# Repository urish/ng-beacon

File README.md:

# ng-beacon

[Physical Web Beacon](https://medium.com/@urish/exploring-the-physical-web-without-buying-beacons-efae51e36c2e) shaped after the [Angular](https://angular.io) logo with JavaScript support

Copyright (C) 2016, 2017 Uri Shaked

## Build your own beacon

Check out the [BOM](BOM.md) file for the list of materials. In addition, you need to get the [PCB](hardware/) printed, I got mine from [PCBWay](http://www.pcbway.com).

## Features

- Physical Web (Eddystone) Beacon
- iBeacon
- Built-in [JavaScript Interpreter](https://www.espruino.com/Reference)
- Fully programmable via JavaScript
- Over-the-air firmware updates
- Prototyping area where you can add your own sensors and extend the board
- Runs of CR2032 / CR2024 coin cell battery, can last for several months
- Built in LED and push button

## Hardware
The board uses the [nRF52832 chip](https://www.nordicsemi.com/eng/Products/Bluetooth-low-energy/nRF52832), which has the following features:

- 32-bit ARM Cortex-M4F Processor running at 64MHz
- 512kB flash + 64kB RAM
- Bluetooth 5 support, up to 2MBPS
- Up to +4dBm output power, -96dBm sensitivity
- 3 PWM, 3 SPI, 2 I²C, Serial UART

## Code samples

Configure the built-in button to control the LED:

    setWatch(() => LED1.toggle(), BTN1, { 
      repeat: true,
      edge: 'falling', 
      debounce: 100
    });

[More code samples](examples/)

## Firmware

The current firmware is based on [Espruino](espruino.com). The latest source code [can be found here](https://github.com/urish/Espruino/tree/ng-beacon), and the most recent firmware build can be found in [this repo](https://github.com/urish/ng-beacon-firmware).

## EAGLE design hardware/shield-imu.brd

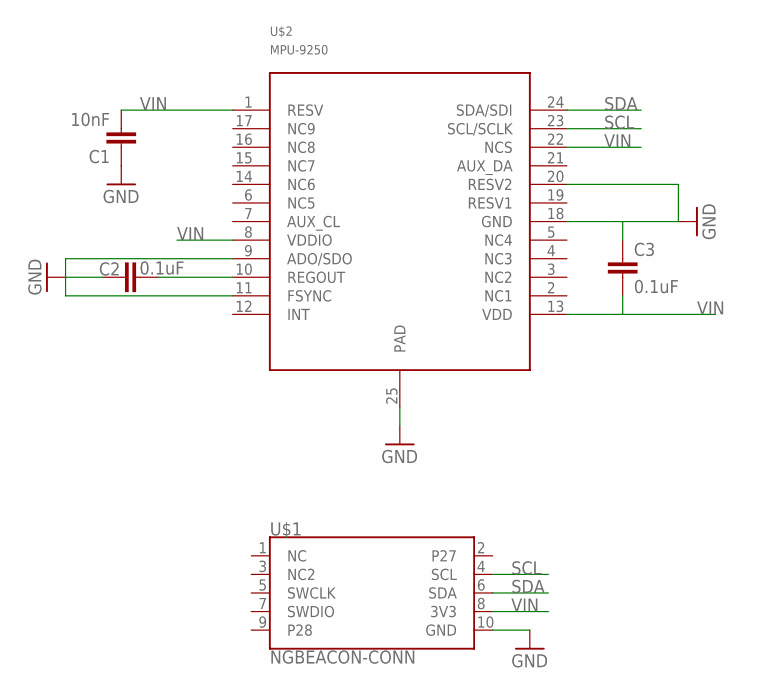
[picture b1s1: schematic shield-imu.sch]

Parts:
C1: 10nF; 0603-CAP
C2, C3: 0.1uF; 0603-CAP
U$1: NGBEACON-CONN; 2X5-PTH-1.27MM
U$2: MPU-9250; LEAD-QFN24

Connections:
GND: C1.1, C2.1, C3.1, U$1.10 (GND), U$2.9 (ADO/SDO), U$2.11 (FSYNC), U$2.18 (GND), U$2.20 (RESV2), U$2.25 (PAD)
unnamed: C2.2, U$2.10 (REGOUT)
SCL: U$1.4 (SCL), U$2.23 (SCL/SCLK)
SDA: U$1.6 (SDA), U$2.24 (SDA/SDI)
VIN: C1.2, C3.2, U$1.8 (3V3), U$2.1 (RESV), U$2.8 (VDDIO), U$2.13 (VDD), U$2.22 (NCS)

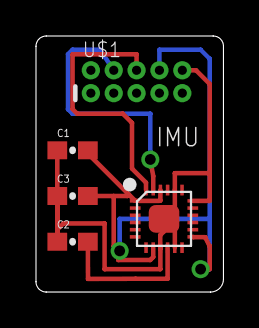
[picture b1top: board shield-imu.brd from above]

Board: 2 copper layers, 10.4 x 14.2 mm, 5 parts (0 on the bottom side), 5 nets.

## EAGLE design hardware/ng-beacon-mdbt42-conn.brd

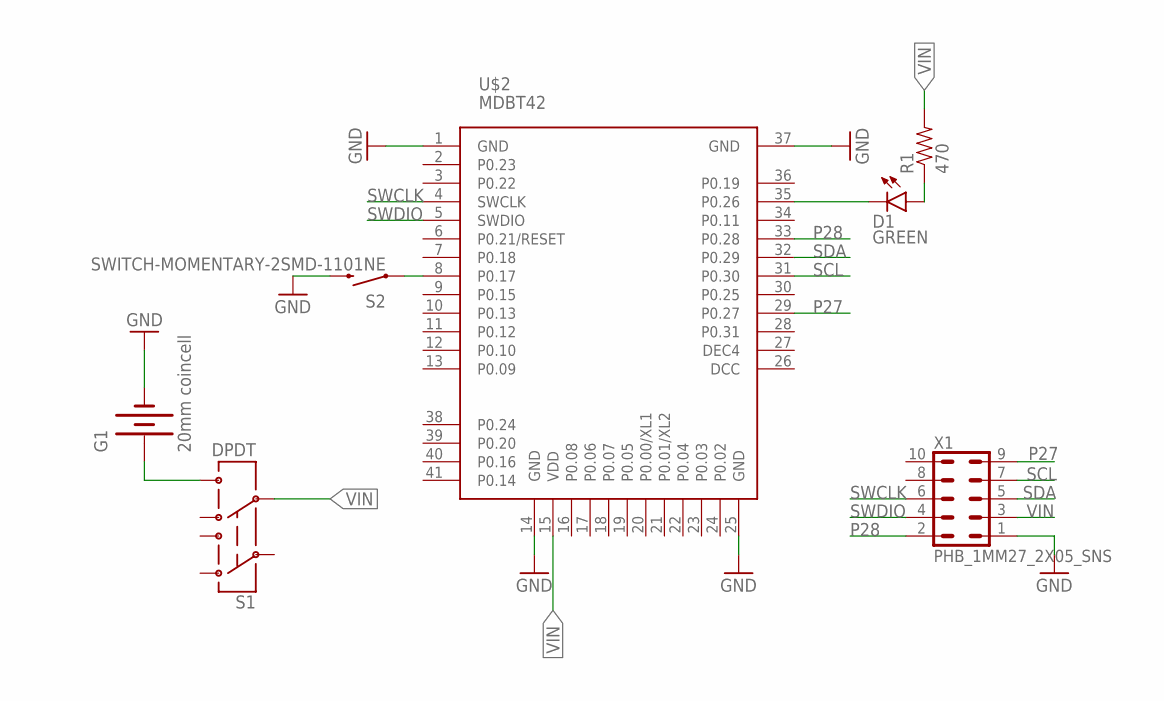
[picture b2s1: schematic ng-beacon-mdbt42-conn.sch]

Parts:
D1: GREEN; LED-0603
G1: 20mm coincell; BATTCON_20MM_4LEGS
R1: 470; 0603-RES
S1: DPDT; AYZ0202
S2: SWITCH-MOMENTARY-2SMD-1101NE; TACTILE-SWITCH-1101NE
U$2: MDBT42
X1: PHB_1MM27_2X05_SNS

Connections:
GND: G1.NEGATIVE (-), S2.2, U$2.1 (GND), U$2.14 (GND), U$2.25 (GND), U$2.37 (GND), X1.1
unnamed: G1.POSITIVE@1 (+), G1.POSITIVE@2 (+), G1.POSITIVE@3 (+), G1.POSITIVE@4 (+), S1.6
unnamed: S2.1, U$2.8 (P0.17)
unnamed: D1.C, U$2.35 (P0.26)
unnamed: D1.A, R1.1
P27: U$2.29 (P0.27), X1.9
P28: U$2.33 (P0.28), X1.2
SCL: U$2.31 (P0.30), X1.7
SDA: U$2.32 (P0.29), X1.5
SWCLK: U$2.4 (SWCLK), X1.6
SWDIO: U$2.5 (SWDIO), X1.4
VIN: R1.2, S1.5, U$2.15 (VDD), X1.3

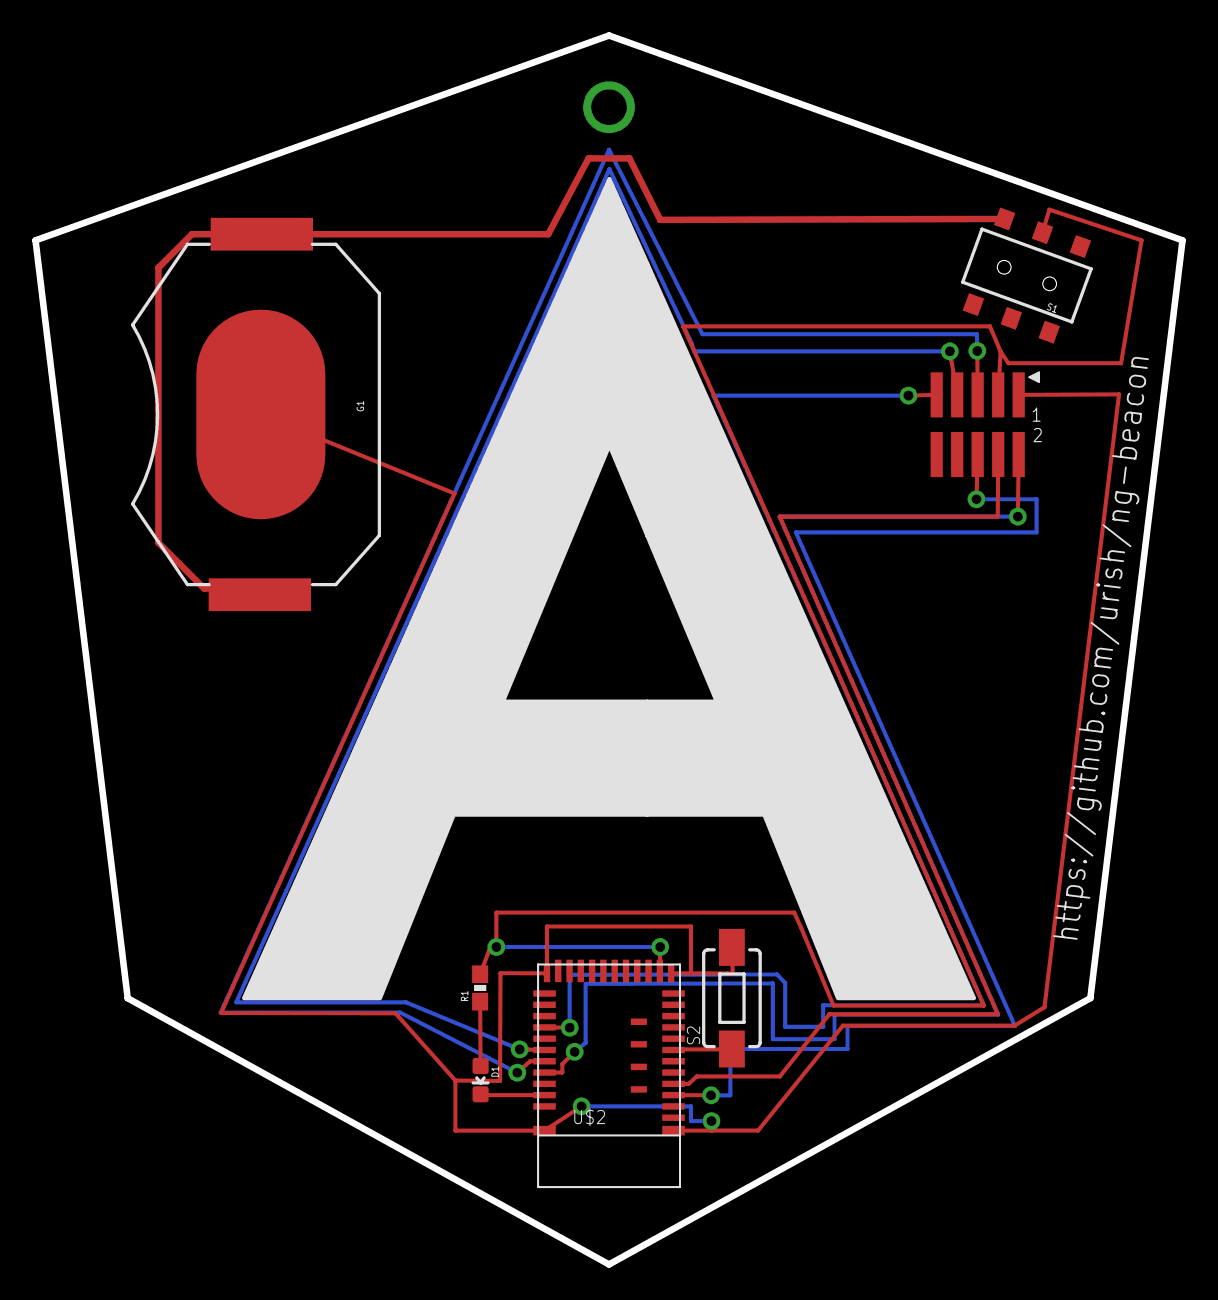
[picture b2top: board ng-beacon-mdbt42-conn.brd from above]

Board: 2 copper layers, 71.1 x 76.2 mm, 7 parts (0 on the bottom side), 12 nets.

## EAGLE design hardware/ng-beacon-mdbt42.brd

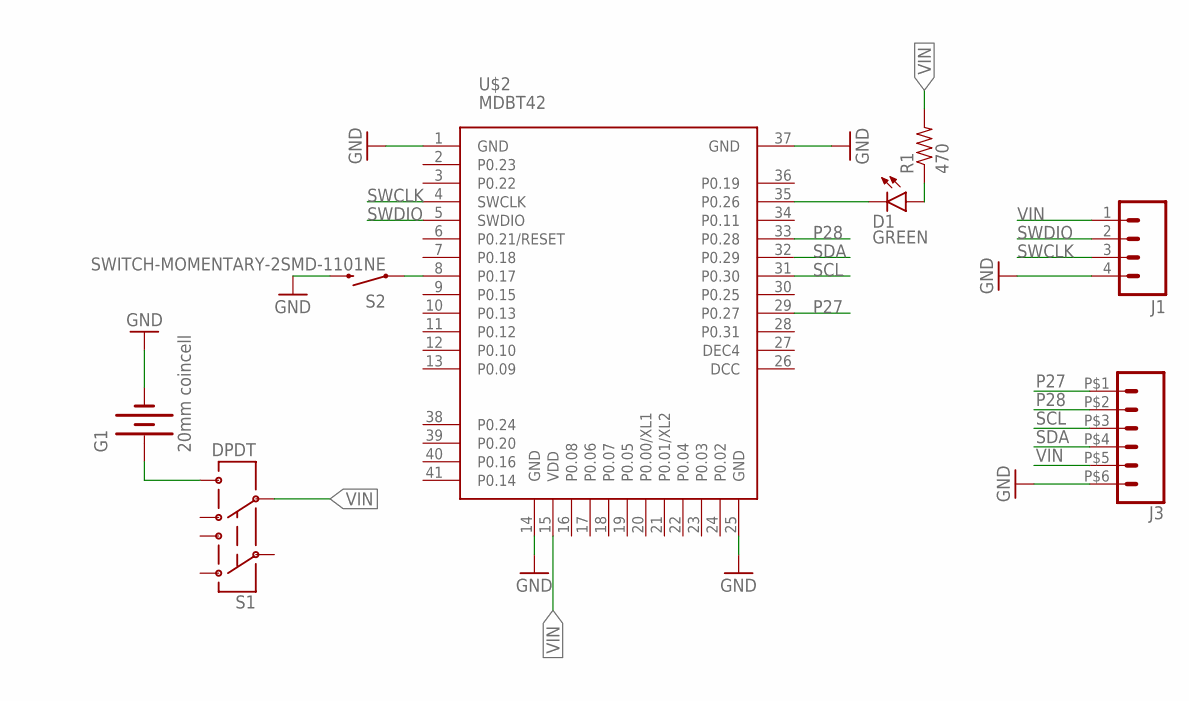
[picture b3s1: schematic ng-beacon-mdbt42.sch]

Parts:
D1: GREEN; LED-0603
G1: 20mm coincell; BATTCON_20MM_4LEGS
J1: M04LOCK; 1X04_LOCK
J3: CONN_06; PROTO4X6
R1: 470; 0603-RES
S1: DPDT; AYZ0202
S2: SWITCH-MOMENTARY-2SMD-1101NE; TACTILE-SWITCH-1101NE
U$2: MDBT42

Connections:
GND: G1.NEGATIVE (-), J1.4, J3.P$6 (6), S2.2, U$2.1 (GND), U$2.14 (GND), U$2.25 (GND), U$2.37 (GND)
unnamed: G1.POSITIVE@1 (+), G1.POSITIVE@2 (+), G1.POSITIVE@3 (+), G1.POSITIVE@4 (+), S1.6
unnamed: S2.1, U$2.8 (P0.17)
unnamed: D1.C, U$2.35 (P0.26)
unnamed: D1.A, R1.1
P27: J3.P$1 (1), U$2.29 (P0.27)
P28: J3.P$2 (2), U$2.33 (P0.28)
SCL: J3.P$3 (3), U$2.31 (P0.30)
SDA: J3.P$4 (4), U$2.32 (P0.29)
SWCLK: J1.3, U$2.4 (SWCLK)
SWDIO: J1.2, U$2.5 (SWDIO)
VIN: J1.1, J3.P$5 (5), R1.2, S1.5, U$2.15 (VDD)

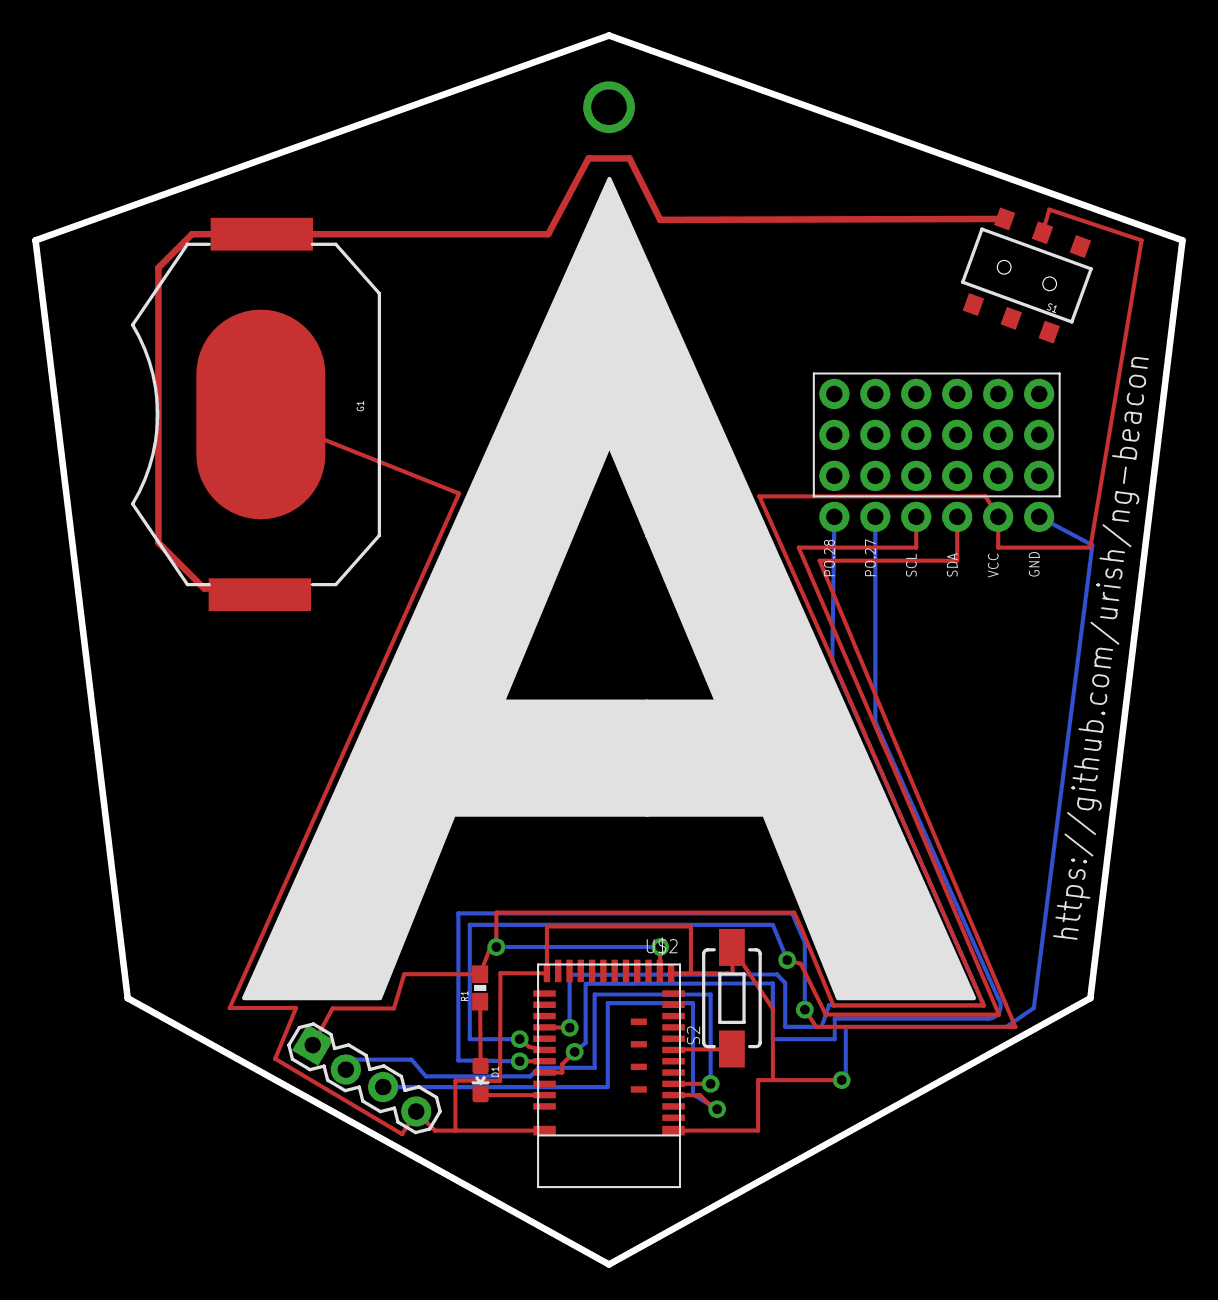
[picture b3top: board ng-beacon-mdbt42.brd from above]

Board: 2 copper layers, 71.1 x 76.2 mm, 8 parts (0 on the bottom side), 12 nets.

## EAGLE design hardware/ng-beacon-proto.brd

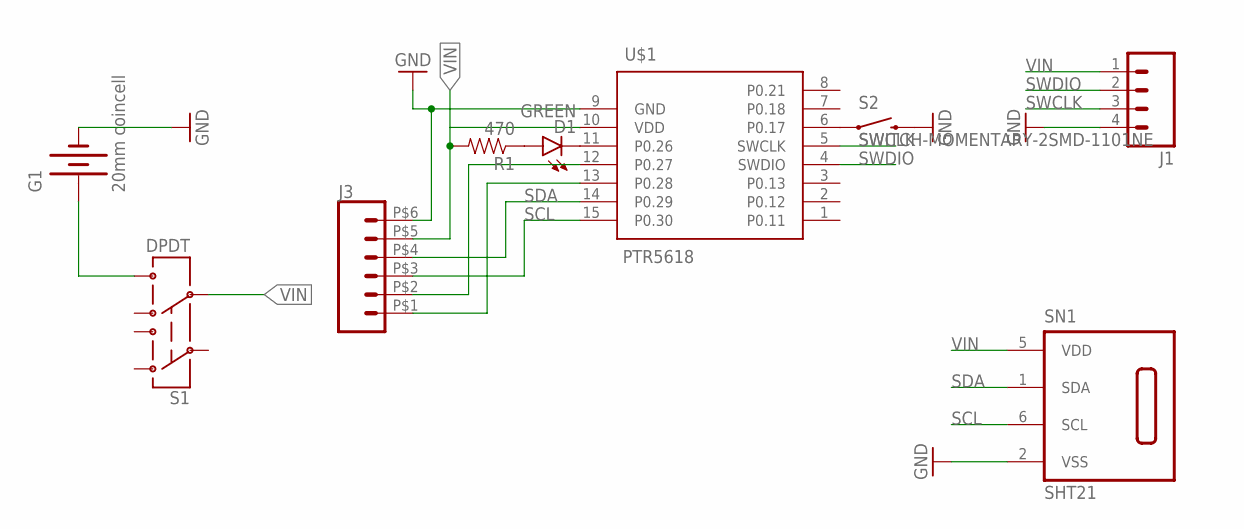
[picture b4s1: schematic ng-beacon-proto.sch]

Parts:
D1: GREEN; LED-0603
G1: 20mm coincell; BATTCON_20MM_4LEGS
J1: M04LOCK; 1X04_LOCK
J3: CONN_06; PROTO4X6
R1: 470; 0603-RES
S1: DPDT; AYZ0202
S2: SWITCH-MOMENTARY-2SMD-1101NE; TACTILE-SWITCH-1101NE
SN1: SHT21; DFN6/SHT
U$1: PTR5618; PTR5518

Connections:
GND: G1.NEGATIVE (-), J1.4, J3.P$6 (6), S2.2, SN1.2 (VSS), U$1.9 (GND)
unnamed: G1.POSITIVE@1 (+), G1.POSITIVE@2 (+), G1.POSITIVE@3 (+), G1.POSITIVE@4 (+), S1.6
unnamed: S2.1, U$1.6 (P0.17)
unnamed: J3.P$2 (2), U$1.12 (P0.27)
unnamed: J3.P$1 (1), U$1.13 (P0.28)
unnamed: D1.C, U$1.11 (P0.26)
unnamed: D1.A, R1.1
SCL: J3.P$3 (3), SN1.6 (SCL), U$1.15 (P0.30)
SDA: J3.P$4 (4), SN1.1 (SDA), U$1.14 (P0.29)
SWCLK: J1.3, U$1.5 (SWCLK)
SWDIO: J1.2, U$1.4 (SWDIO)
VIN: J1.1, J3.P$5 (5), R1.2, S1.5, SN1.5 (VDD), U$1.10 (VDD)

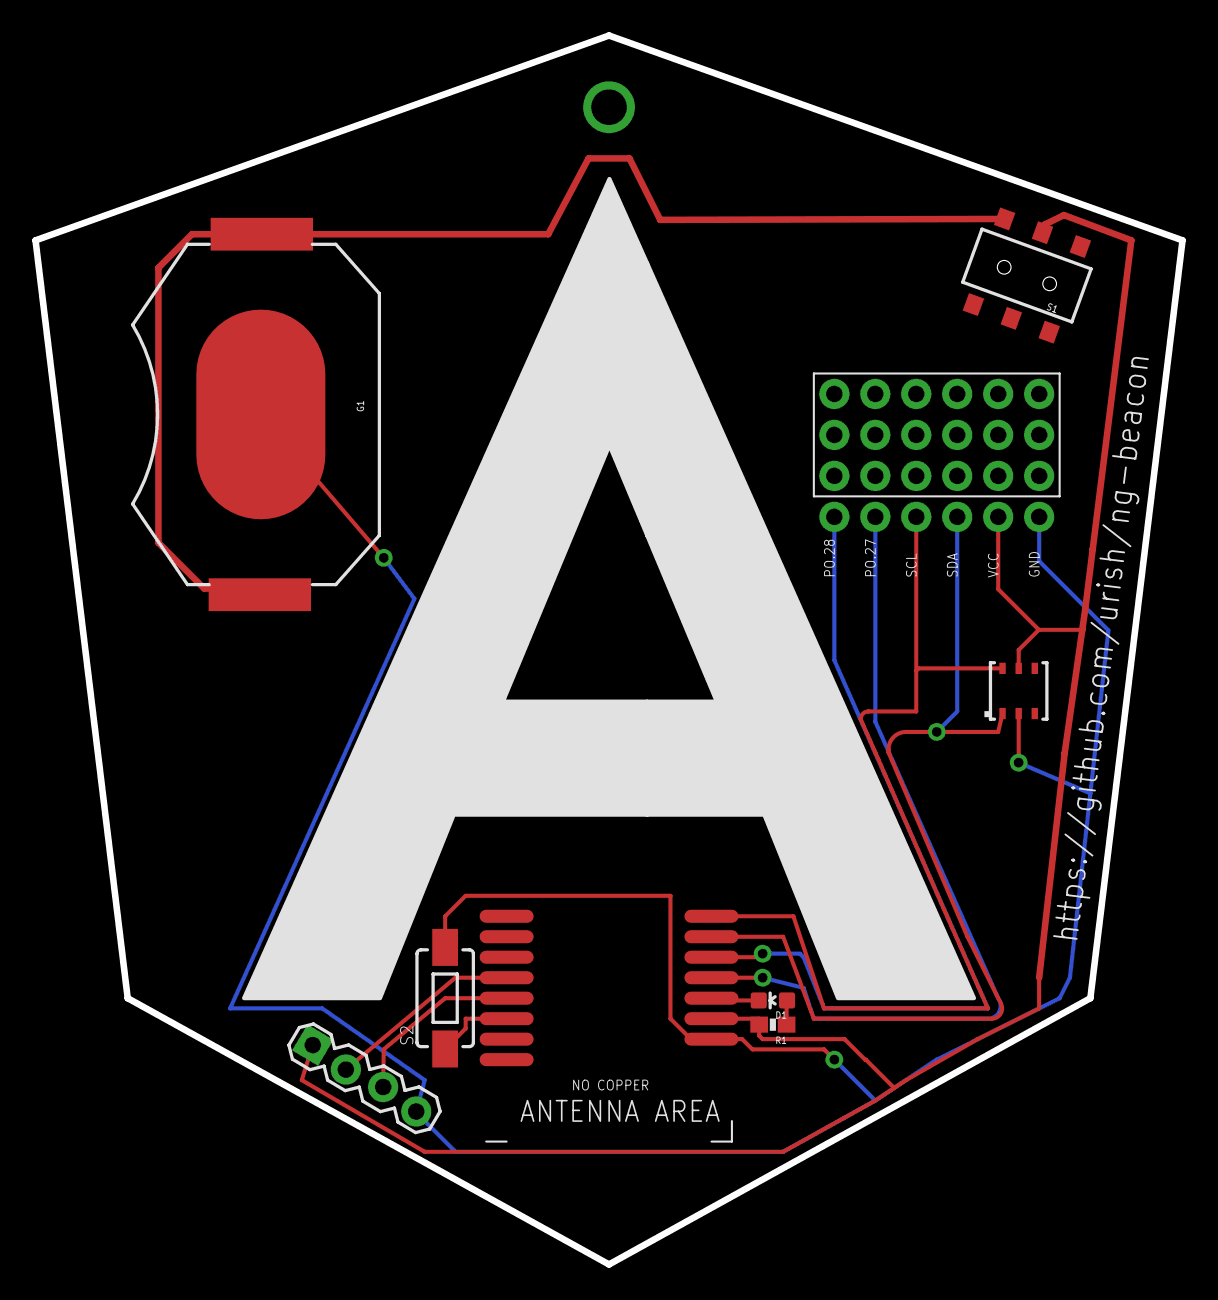
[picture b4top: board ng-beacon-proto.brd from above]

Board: 2 copper layers, 71.1 x 76.2 mm, 9 parts (0 on the bottom side), 12 nets.

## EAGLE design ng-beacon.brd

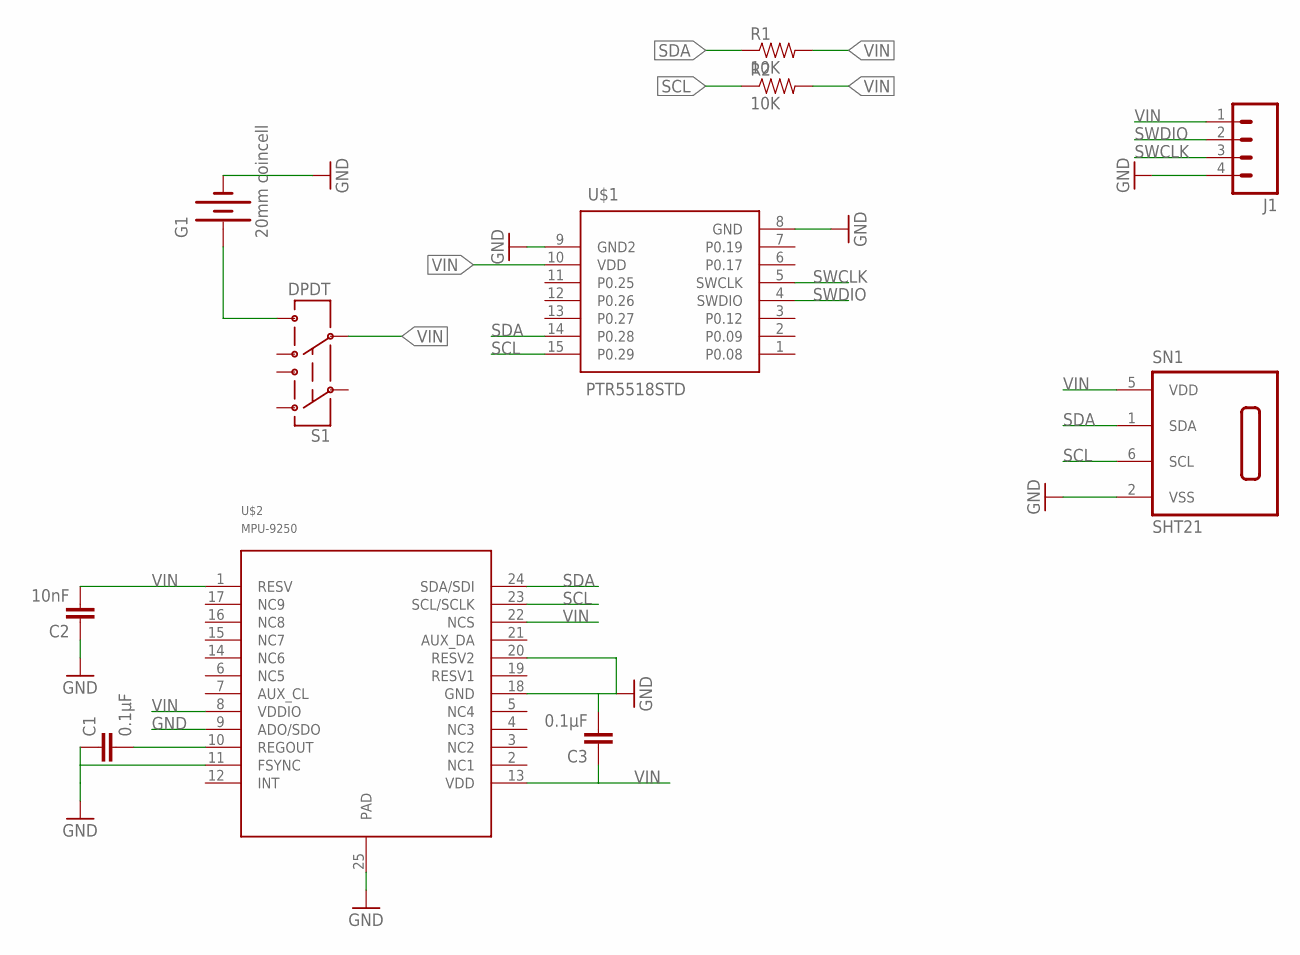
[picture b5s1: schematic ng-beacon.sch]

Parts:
C1, C3: 0.1µF; 0603-CAP
C2: 10nF; 0603-CAP
G1: 20mm coincell; BATTCON_20MM_4LEGS
J1: M04LOCK; 1X04_LOCK
R1, R2: 10K; 0603-RES
S1: DPDT; AYZ0202
SN1: SHT21; DFN6/SHT
U$1: PTR5518STD; PTR5518
U$2: MPU-9250; LEAD-QFN24

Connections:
GND: C1.1, C2.1, C3.2, G1.NEGATIVE (-), J1.4, SN1.2 (VSS), U$1.8 (GND), U$1.9 (GND2), U$2.9 (ADO/SDO), U$2.11 (FSYNC), U$2.18 (GND), U$2.20 (RESV2), U$2.25 (PAD)
unnamed: G1.POSITIVE@1 (+), G1.POSITIVE@2 (+), G1.POSITIVE@3 (+), G1.POSITIVE@4 (+), S1.6
unnamed: C1.2, U$2.10 (REGOUT)
SCL: R2.1, SN1.6 (SCL), U$1.15 (P0.29), U$2.23 (SCL/SCLK)
SDA: R1.1, SN1.1 (SDA), U$1.14 (P0.28), U$2.24 (SDA/SDI)
SWCLK: J1.3, U$1.5 (SWCLK)
SWDIO: J1.2, U$1.4 (SWDIO)
VIN: C2.2, C3.1, J1.1, R1.2, R2.2, S1.5, SN1.5 (VDD), U$1.10 (VDD), U$2.1 (RESV), U$2.8 (VDDIO), U$2.13 (VDD), U$2.22 (NCS)

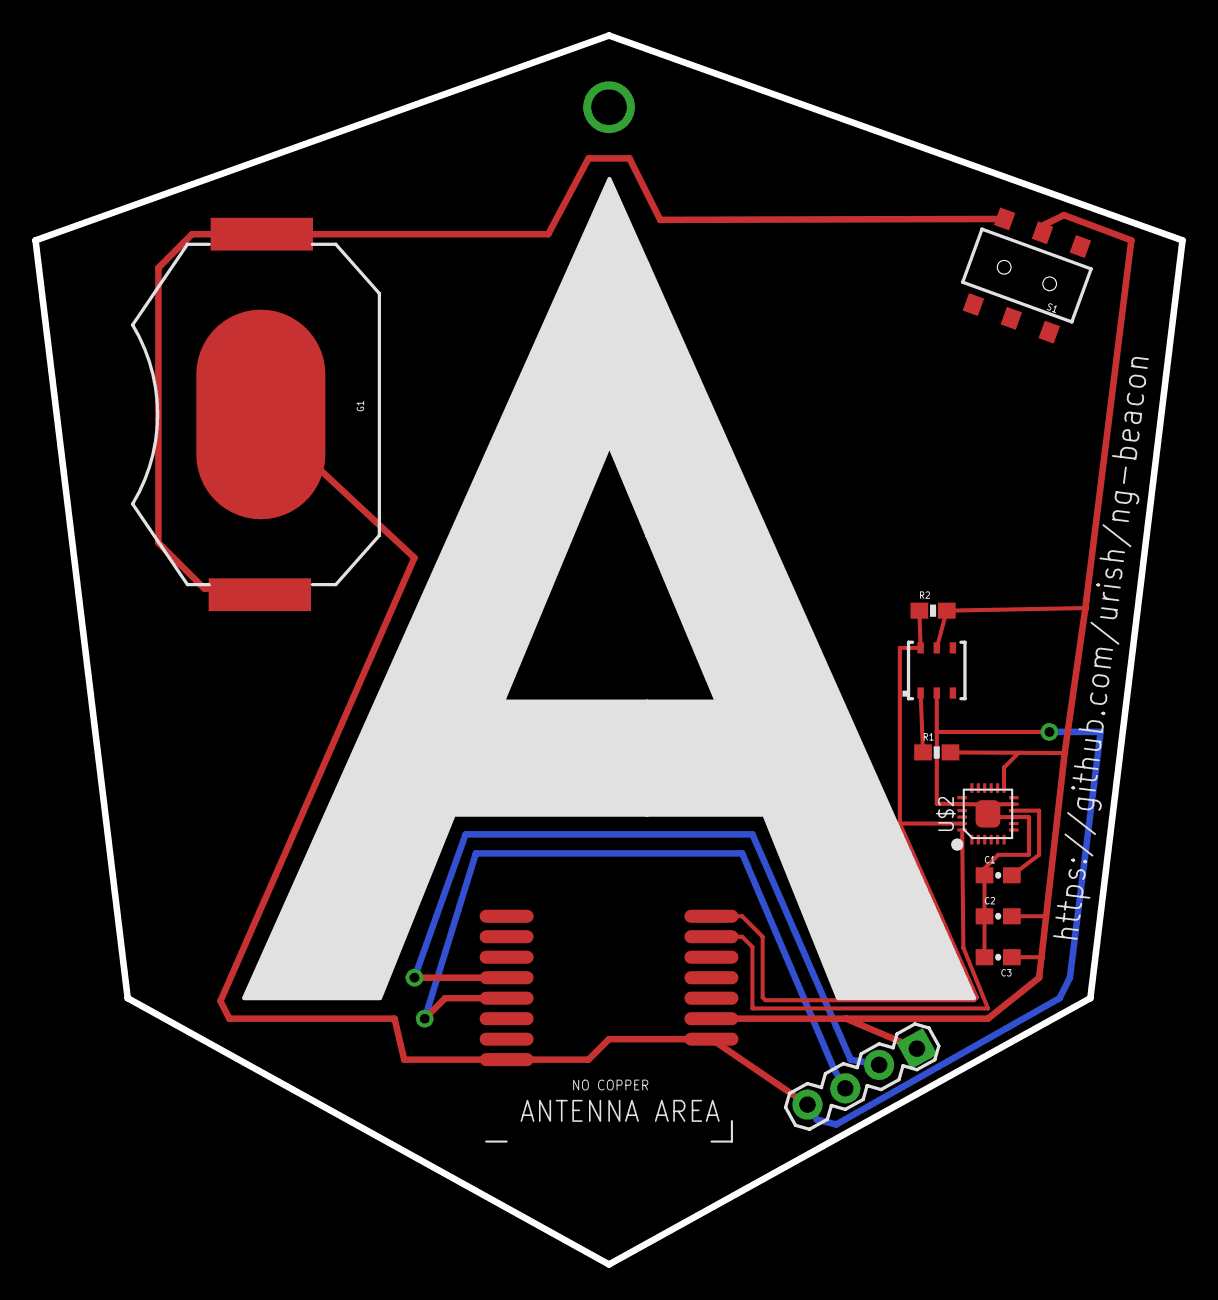
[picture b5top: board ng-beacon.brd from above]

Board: 2 copper layers, 71.1 x 76.2 mm, 11 parts (0 on the bottom side), 8 nets.

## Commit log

2016-12-27 update board layout
2016-12-27 add switch
2016-12-27 add programming port
2016-12-27 add temperature sensor
2016-12-31 fix github repo url text
2017-01-01 replace battery connector
2017-01-01 Add sketchup model of SHT20
2017-01-01 add sketchup model of PTR5518
2017-01-01 remove temp sensor label
2017-01-05 add README + renders
2017-01-05 remove drills from PTR5518 package
2017-01-05 improve routing, switch to SparkFun DRU
2017-01-15 Add initial Physical Web firmware
2017-01-24 feat(firmware): temperature sensor support
2017-01-31 feat(pcb): initial effort adding an IMU
    MPU-9250: includes accelerometer, gyroscope, compass
2017-01-31 refactor: move pcb files to `hardware` directory
2017-01-31 DOC: update README, add BOM
2017-01-31 fix(pcb): remove I2C pullup resistors
    it works fine without them, as the nRF51 has internal pullups
2017-02-20 refactor: switch to MDBT42 module
    nRF52, more pins and smaller footprint
2017-02-20 add reset pads (sort of)
2017-02-21 fix: change shape of boot loader pads
2017-02-21 feat: add DFU pads
2017-03-02 fix: update board layout for PTR5618
2017-03-13 Add a prototype area with PO.26, 27, SDA, and SCL.
2017-03-14 Convert to PTR5618, export components to project-specific library.
2017-03-16 move the proto version of a different file
2017-03-31 feat: add LED + BUTTON to the proto board
2017-03-31 doc: update about JavaScript support
2017-04-05 doc: update BOM
2017-04-05 doc: fix heading
2017-04-20 feat: add board layout for the mdbt42 module
2017-05-08 feat: add a small on-board connector for shields
2017-05-09 cleanup ng-beacon.lbr
2017-05-09 feat: IMU shield
2017-05-09 feat: add ng-beacon shield connector to ng-beacon.lbr
2017-05-09 feat: jlink shield
2017-07-29 doc: update features + hardware sections
2017-07-29 feat: add JavaScript code samples
2017-07-29 doc: Add code samples section to README

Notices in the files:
parts and their libraries:
SparkFun-LED: Licensing: Creative Commons ShareAlike 4.0 International - https://creativecommons.org/licenses/by-sa/4.0
sensirion: Copyright (C) 2011, Bob Starr
